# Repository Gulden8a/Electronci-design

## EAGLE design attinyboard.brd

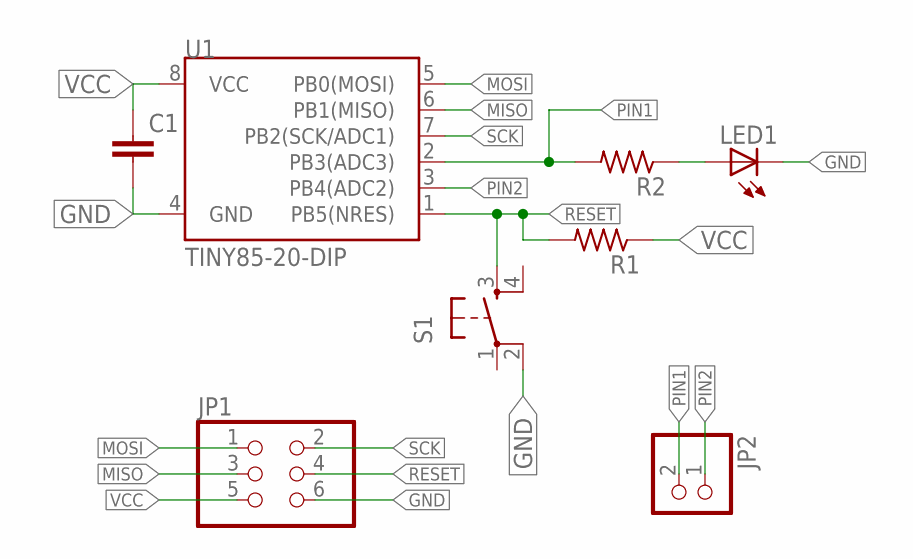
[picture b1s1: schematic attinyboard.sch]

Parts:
C1: C-EU025-030X050; C025-030X050
JP1: PINHD-2X3; 2X03
JP2: PINHD-1X2; 1X02
LED1: LED5MM
R1, R2: R-US_0204/7; 0204/7
S1: TAC_SWITCHPTH; TACTILE-PTH
U1: TINY85-20-DIP; DIP08

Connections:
GND: C1.2, JP1.6, LED1.K (C), S1.2, U1.4 (GND)
MISO: JP1.3, U1.6 (PB1(MISO))
MOSI: JP1.1, U1.5 (PB0(MOSI))
unnamed: LED1.A, R2.1
PIN1: JP2.2, R2.2, U1.2 (PB3(ADC3))
PIN2: JP2.1, U1.3 (PB4(ADC2))
RESET: JP1.4, R1.2, S1.3, U1.1 (PB5(NRES))
SCK: JP1.2, U1.7 (PB2(SCK/ADC1))
VCC: C1.1, JP1.5, R1.1, U1.8 (VCC)

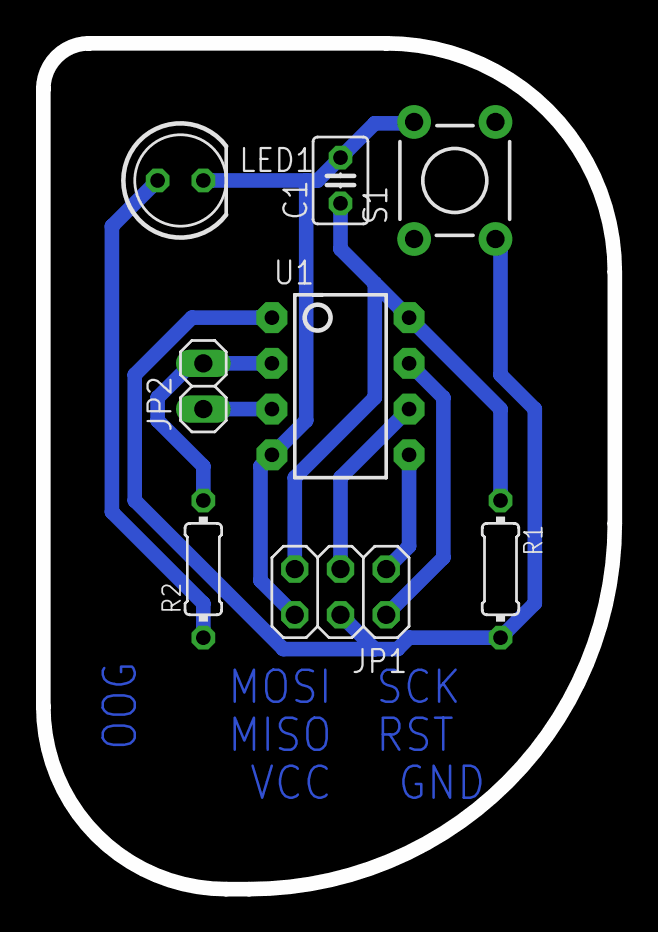
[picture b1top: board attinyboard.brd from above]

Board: 2 copper layers, 31.8 x 47.0 mm, 8 parts (0 on the bottom side), 9 nets.

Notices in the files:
parts and their libraries:
SparkFun-Retired: Licensing:Creative Commons ShareAlike 4.0 International - https://creativecommons.org/licenses/by-sa/4.0
